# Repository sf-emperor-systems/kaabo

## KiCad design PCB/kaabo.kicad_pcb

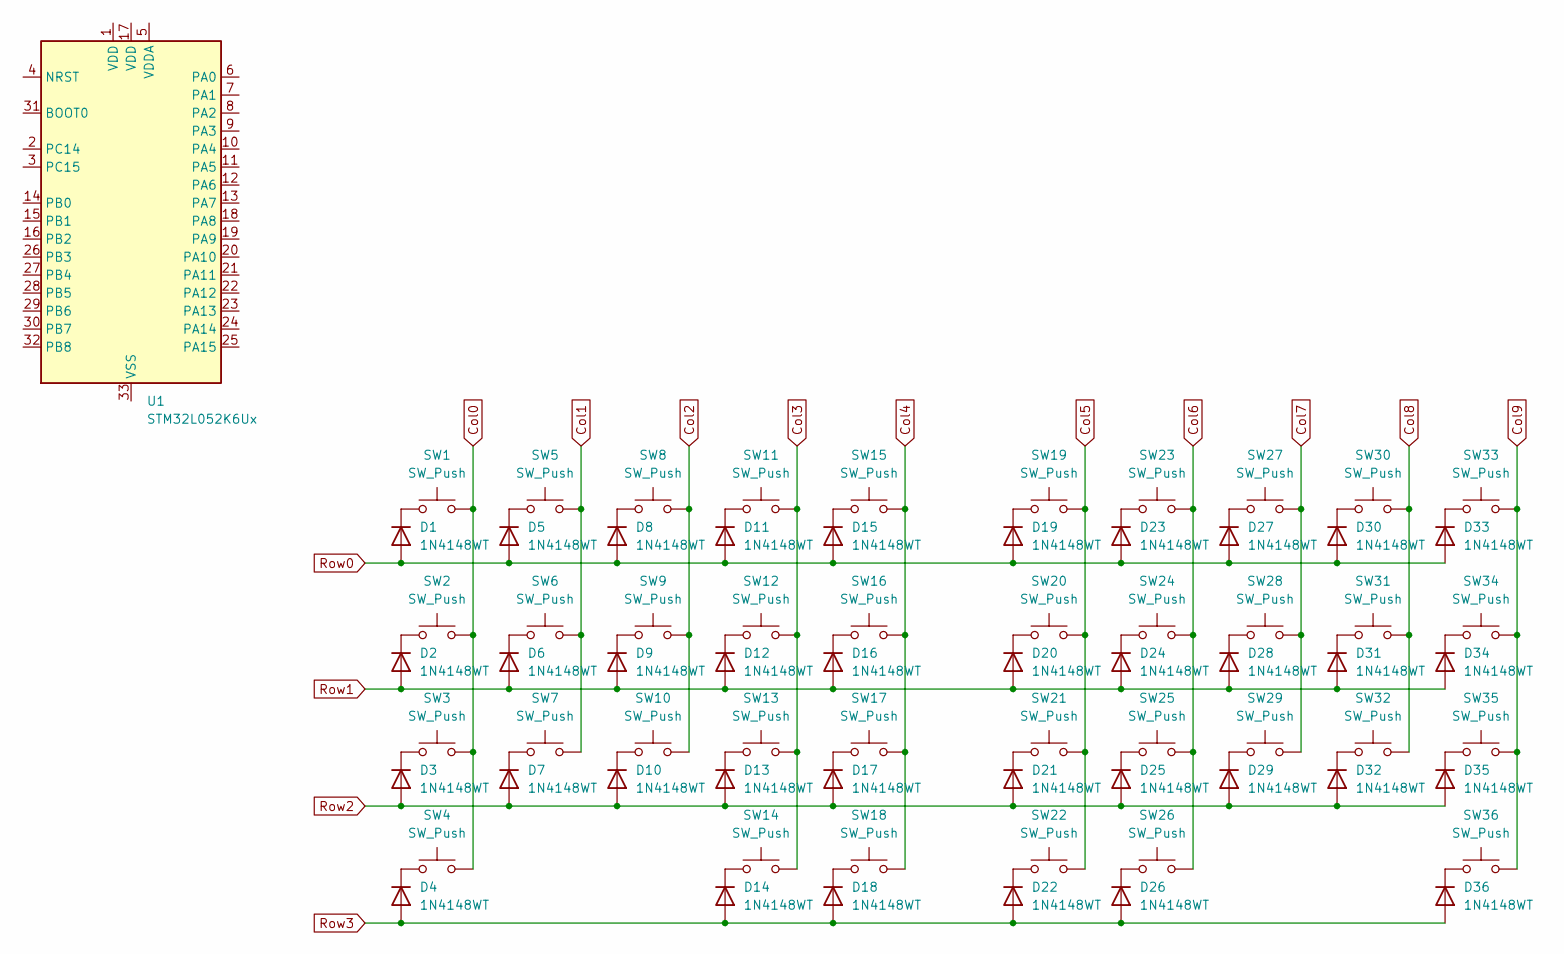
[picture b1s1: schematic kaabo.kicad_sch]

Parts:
D1, D2, D3, D4, D5, D6, D7, D8, D9, D10, D11, D12, D13, D14, D15, D16, D17, D18, D19, D20, D21, D22, D23, D24, D25, D26, D27, D28, D29, D30, D31, D32, D33, D34, D35, D36: 1N4148WT; D_SOD-323
SW1, SW2, SW3, SW5, SW6, SW7, SW8, SW9, SW10, SW11, SW12, SW13, SW14, SW15, SW16, SW17, SW19, SW20, SW21, SW23, SW24, SW25, SW26, SW27, SW28, SW29, SW30, SW31, SW32, SW33, SW34, SW35: SW_Push; SW_choc_v1+v2_HS_CPG135001S30_1u
SW4, SW18, SW22, SW36: SW_Push; SW_choc_v1+v2_HS_CPG135001S30_1.5u
U1: STM32L052K6Ux; QFN-32-1EP_5x5mm_P0.5mm_EP3.45x3.45mm

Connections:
Col0: SW1.2, SW2.2, SW3.2, SW4.2
Col1: SW5.2, SW6.2, SW7.2
Col2: SW8.2, SW9.2, SW10.2
Col3: SW11.2, SW12.2, SW13.2, SW14.2
Col4: SW15.2, SW16.2, SW17.2, SW18.2
Col5: SW19.2, SW20.2, SW21.2, SW22.2
Col6: SW23.2, SW24.2, SW25.2, SW26.2
Col7: SW27.2, SW28.2, SW29.2
Col8: SW30.2, SW31.2, SW32.2
Col9: SW33.2, SW34.2, SW35.2, SW36.2
unnamed: D1.1 (K), SW1.1
unnamed: D2.1 (K), SW2.1
unnamed: D3.1 (K), SW3.1
unnamed: D4.1 (K), SW4.1
unnamed: D5.1 (K), SW5.1
unnamed: D6.1 (K), SW6.1
unnamed: D7.1 (K), SW7.1
unnamed: D8.1 (K), SW8.1
unnamed: D9.1 (K), SW9.1
unnamed: D10.1 (K), SW10.1
unnamed: D11.1 (K), SW11.1
unnamed: D12.1 (K), SW12.1
unnamed: D13.1 (K), SW13.1
unnamed: D14.1 (K), SW14.1
unnamed: D15.1 (K), SW15.1
unnamed: D16.1 (K), SW16.1
unnamed: D17.1 (K), SW17.1
unnamed: D18.1 (K), SW18.1
unnamed: D19.1 (K), SW19.1
unnamed: D20.1 (K), SW20.1
unnamed: D21.1 (K), SW21.1
unnamed: D22.1 (K), SW22.1
unnamed: D23.1 (K), SW23.1
unnamed: D24.1 (K), SW24.1
unnamed: D25.1 (K), SW25.1
unnamed: D26.1 (K), SW26.1
unnamed: D27.1 (K), SW27.1
unnamed: D28.1 (K), SW28.1
unnamed: D29.1 (K), SW29.1
unnamed: D30.1 (K), SW30.1
unnamed: D31.1 (K), SW31.1
unnamed: D32.1 (K), SW32.1
unnamed: D33.1 (K), SW33.1
unnamed: D34.1 (K), SW34.1
unnamed: D35.1 (K), SW35.1
unnamed: D36.1 (K), SW36.1
Row0: D1.2 (A), D5.2 (A), D8.2 (A), D11.2 (A), D15.2 (A), D19.2 (A), D23.2 (A), D27.2 (A), D30.2 (A), D33.2 (A)
Row1: D2.2 (A), D6.2 (A), D9.2 (A), D12.2 (A), D16.2 (A), D20.2 (A), D24.2 (A), D28.2 (A), D31.2 (A), D34.2 (A)
Row2: D3.2 (A), D7.2 (A), D10.2 (A), D13.2 (A), D17.2 (A), D21.2 (A), D25.2 (A), D29.2 (A), D32.2 (A), D35.2 (A)
Row3: D4.2 (A), D14.2 (A), D18.2 (A), D22.2 (A), D26.2 (A), D36.2 (A)

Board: 2 copper layers, 73 parts (72 on the bottom side), 50 nets, no tracks yet.

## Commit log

2026-03-02 actually adding the stuff
2026-03-02 rename kicad folder
2026-03-02 removed wacky and crazy file
2026-03-02 slight restructure in kicad/
